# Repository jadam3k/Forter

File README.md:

# Forter

## Overview
This project is a fully designed Microcontroller made with ESP32-S3. it has got 20 IO pins with ESP32 mapping so you can map them, and 4 power pins with gnd. Project also includes 4 mouting holes for screwdriwers with thermical protection
No filmware needed
## Why I Made This
I made this because im running out of MCU's lol

## Features
- Nice microcontroller for nice projects ;)

## 3D Model

## PCB

ERRORS

two termical errors but that will work

## Wiring Diagram

## Files Included
This repository contains everything needed to review and reproduce the project:

- `/PCB` – source CAD files and exported STEP model
- `BOM.csv` – bill of materials with links

  Because This is not cad project and im only making pcb im staying with that

## How to flash ESP32-S3
You dont have to do anything. use arduinoIDE

## BOM

| Name | Purpose | Quantity | Total Cost (USD) | Link | Distributor |
|------|--------|----------|------------------|------|------------|
| AMS1117 | 5V to 3.3V regulator | 5 | 1.13 | https://www.lcsc.com/product-detail/C6186.html | LCSC |
| PCB | PCB manufacturing | 5 | 2.00 | — | JLCPCB |
| ESP32-S3-WROOM-1-N8 | Main microcontroller | 1 | 4.79 | https://www.lcsc.com/product-detail/C2913198.html | LCSC |
| 100mW 240Ω 75V Resistor | LED current limiting | 100 | 0.16 | https://www.lcsc.com/product-detail/C114629.html | LCSC |
| 100mW 10kΩ 75V | Pull-up / general use | 100 | 0.14 | https://www.lcsc.com/product-detail/C98220.html | LCSC |
| 5.1kΩ ±1% 100mW 0603 Resistor | USB-C configuration | 100 | 0.12 | https://www.lcsc.com/product-detail/C2907044.html | LCSC |
| 22Ω ±1% 100mW 0603 Resistor | Signal lines (e.g. USB) | 100 | 0.13 | https://www.lcsc.com/product-detail/C23345.html | LCSC |
| USB-C Conn | Power + data connector | 5 | 0.84 | https://www.lcsc.com/product-detail/C165948.html | LCSC |
| Emerald Green LED DIODE | Power indication | 100 | 0.51 | https://www.lcsc.com/product-detail/C965804.html | LCSC |
| 1uF ±10% 50V Ceramic Capacitor | Decoupling | 50 | 0.39 | https://www.lcsc.com/product-detail/C15849.html | LCSC |
| 100nF ±10% 50V Ceramic Capacitor | Decoupling | 200 | 0.64 | https://www.lcsc.com/product-detail/C14663.html | LCSC |
| 10uF ±10% 10V Ceramic Capacitor | Bulk capacitance | 50 | 0.40 | https://www.lcsc.com/product-detail/C19702.html | LCSC |

Additionally (things I already have at home: Buttons and pins. I didn’t include them because I can’t add items on the stasis site that I don’t want to receive grant for.

You can use this all. dont forget to star my work :))

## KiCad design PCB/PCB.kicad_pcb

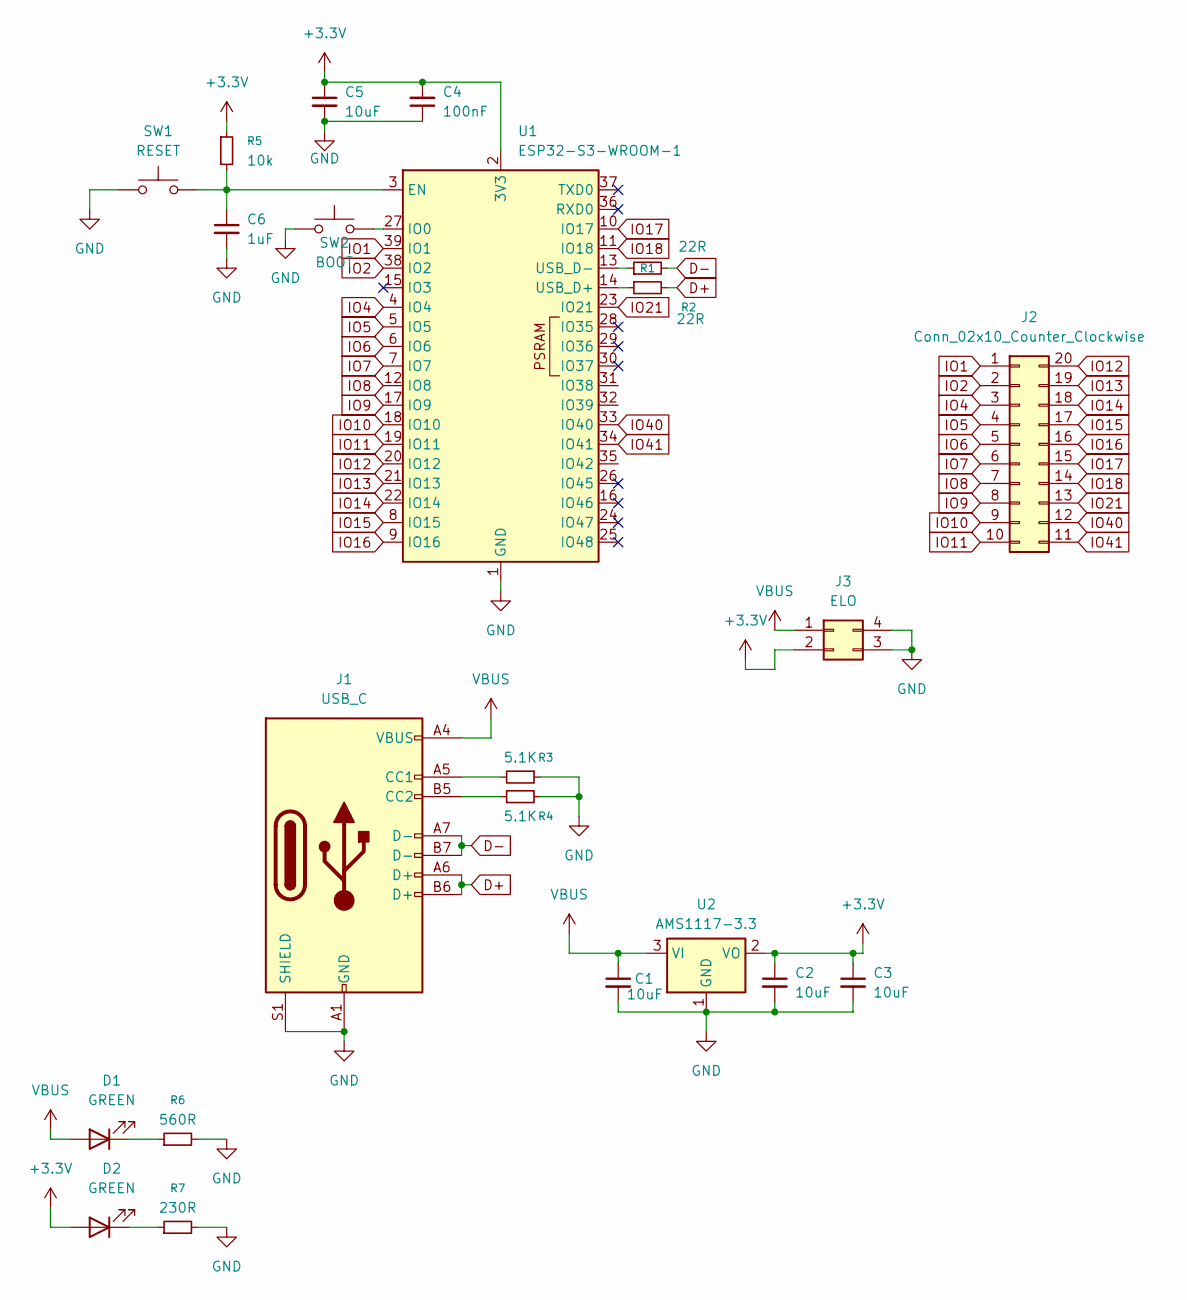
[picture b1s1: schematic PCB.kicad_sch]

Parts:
C1, C2, C3, C5: 10uF; C_0603_1608Metric_Pad1.08x0.95mm_HandSolder
C4: 100nF; C_0603_1608Metric_Pad1.08x0.95mm_HandSolder
C6: 1uF; C_0603_1608Metric_Pad1.08x0.95mm_HandSolder
D1, D2: GREEN; LED_0603_1608Metric_Pad1.05x0.95mm_HandSolder
J1: USB_C; USB_C_Receptacle_HRO_TYPE-C-31-M-12
J2: Conn_02x10_Counter_Clockwise; PinHeader_2x10_P2.54mm_Vertical
J3: ELO; PinHeader_2x02_P2.54mm_Vertical
R1, R2: 22R; R_0603_1608Metric_Pad0.98x0.95mm_HandSolder
R3, R4: 5.1K; R_0603_1608Metric_Pad0.98x0.95mm_HandSolder
R5: 10k; R_0603_1608Metric_Pad0.98x0.95mm_HandSolder
R6: 560R; R_0603_1608Metric_Pad0.98x0.95mm_HandSolder
R7: 230R; R_0603_1608Metric_Pad0.98x0.95mm_HandSolder
SW1: RESET; SW_PUSH_6mm
SW2: BOOT; SW_PUSH_6mm
U1: ESP32-S3-WROOM-1
U2: AMS1117-3.3; SOT-223-3_TabPin2

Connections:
+3.3V: C2.1, C3.1, C4.2, C5.1, D2.2 (A), J3.2, R5.1, U1.2 (3V3), U2.2 (VO)
D+: J1.A6 (D+), J1.B6 (D+), R2.2
D-: J1.A7 (D-), J1.B7 (D-), R1.2
GND: C1.2, C2.2, C3.2, C4.1, C5.2, C6.2, J1.A1 (GND), J1.A12 (GND), J1.B1 (GND), J1.B12 (GND), J1.S1 (SHIELD), J3.3, J3.4, R3.1, R4.2, R6.2, R7.2, SW1.1, SW2.1, U1.1 (GND), U1.40 (GND), U1.41 (GND), U2.1 (GND)
IO1: J2.1, U1.39 (IO1)
IO2: J2.2, U1.38 (IO2)
IO4: J2.3, U1.4 (IO4)
IO5: J2.4, U1.5 (IO5)
IO6: J2.5, U1.6 (IO6)
IO7: J2.6, U1.7 (IO7)
IO8: J2.7, U1.12 (IO8)
IO9: J2.8, U1.17 (IO9)
IO10: J2.9, U1.18 (IO10)
IO11: J2.10, U1.19 (IO11)
IO12: J2.20, U1.20 (IO12)
IO13: J2.19, U1.21 (IO13)
IO14: J2.18, U1.22 (IO14)
IO15: J2.17, U1.8 (IO15)
IO16: J2.16, U1.9 (IO16)
IO17: J2.15, U1.10 (IO17)
IO18: J2.14, U1.11 (IO18)
IO21: J2.13, U1.23 (IO21)
IO40: J2.12, U1.33 (IO40)
IO41: J2.11, U1.34 (IO41)
unnamed: D1.1 (K), R6.1
unnamed: D2.1 (K), R7.1
unnamed: J1.A5 (CC1), R3.2
unnamed: J1.B5 (CC2), R4.1
unnamed: C6.1, R5.2, SW1.2, U1.3 (EN)
unnamed: SW2.2, U1.27 (IO0)
unnamed: R2.1, U1.14 (USB_D+)
unnamed: R1.1, U1.13 (USB_D-)
VBUS: C1.1, D1.2 (A), J1.A4 (VBUS), J1.A9 (VBUS), J1.B4 (VBUS), J1.B9 (VBUS), J3.1, U2.3 (VI)

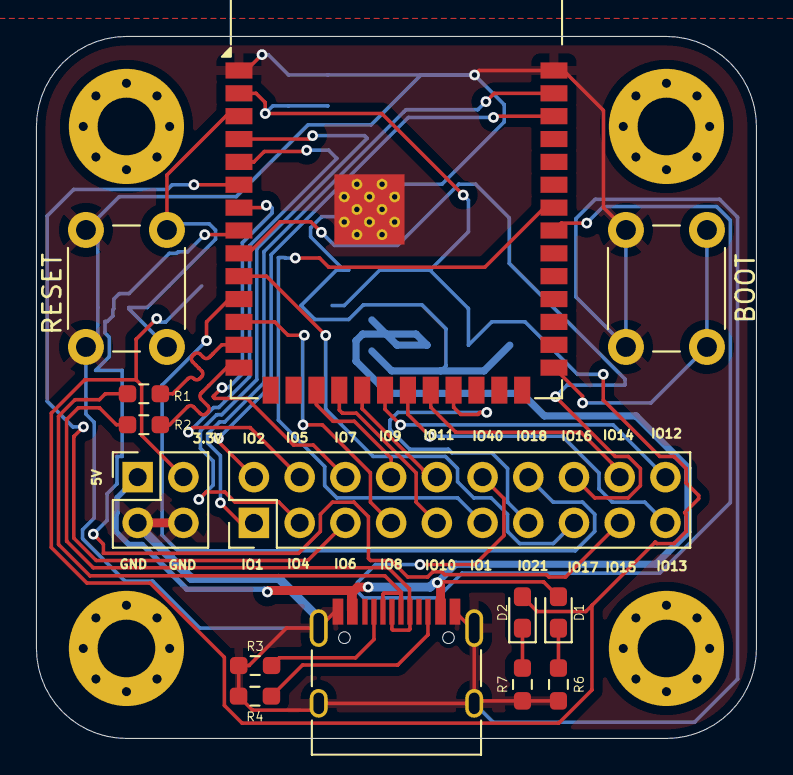
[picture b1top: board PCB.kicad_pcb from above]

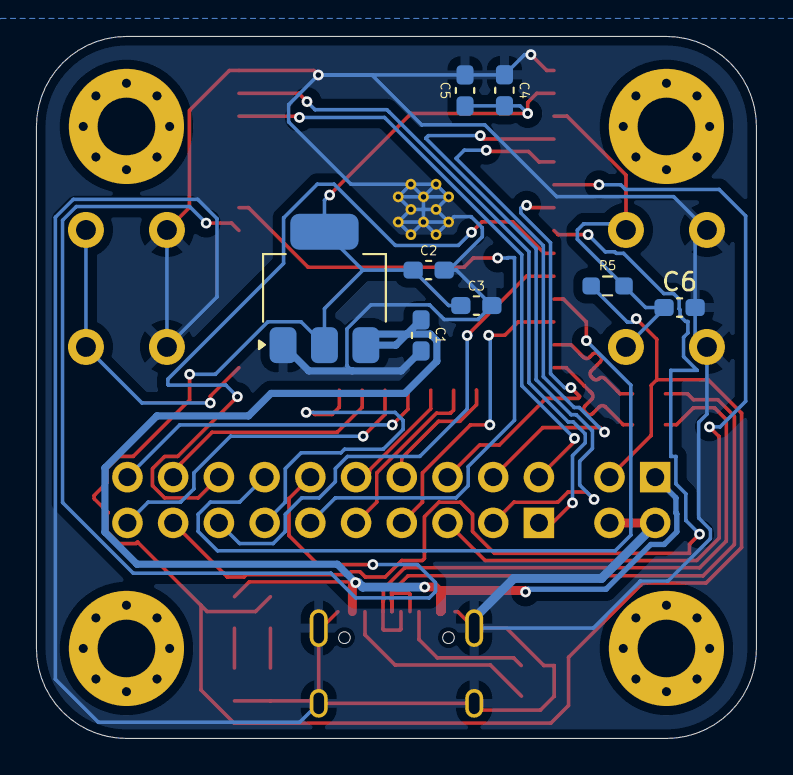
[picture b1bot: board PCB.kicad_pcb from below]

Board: 2 copper layers, 40.0 x 39.0 mm, 22 parts (8 on the bottom side), 33 nets.

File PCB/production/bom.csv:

Designator,Footprint,Quantity,Value,LCSC Part #
"C1, C2, C3, C5",0603,4,10uF,
C4,0603,1,100nF,
C6,0603,1,1uF,
"D1, D2",0603,2,GREEN,
J1,USB_C_Receptacle_HRO_TYPE-C-31-M-12,1,USB_C,
J2,PinHeader_2x10_P2.54mm_Vertical,1,Conn_02x10_Counter_Clockwise,
J3,PinHeader_2x02_P2.54mm_Vertical,1,ELO,
"R1, R2",0603,2,22R,
"R3, R4",0603,2,5.1K,
R5,0603,1,10k,
R6,0603,1,560R,
R7,0603,1,230R,
SW1,SW_PUSH_6mm,1,RESET,
SW2,SW_PUSH_6mm,1,BOOT,
U1,ESP32-S3-WROOM-1,1,ESP32-S3-WROOM-1,
U2,SOT-223-3_TabPin2,1,AMS1117-3.3,

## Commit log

2026-04-07 Enhance README with project details and BOM
    Added detailed project information including overview, features, wiring diagram, and bill of materials.
